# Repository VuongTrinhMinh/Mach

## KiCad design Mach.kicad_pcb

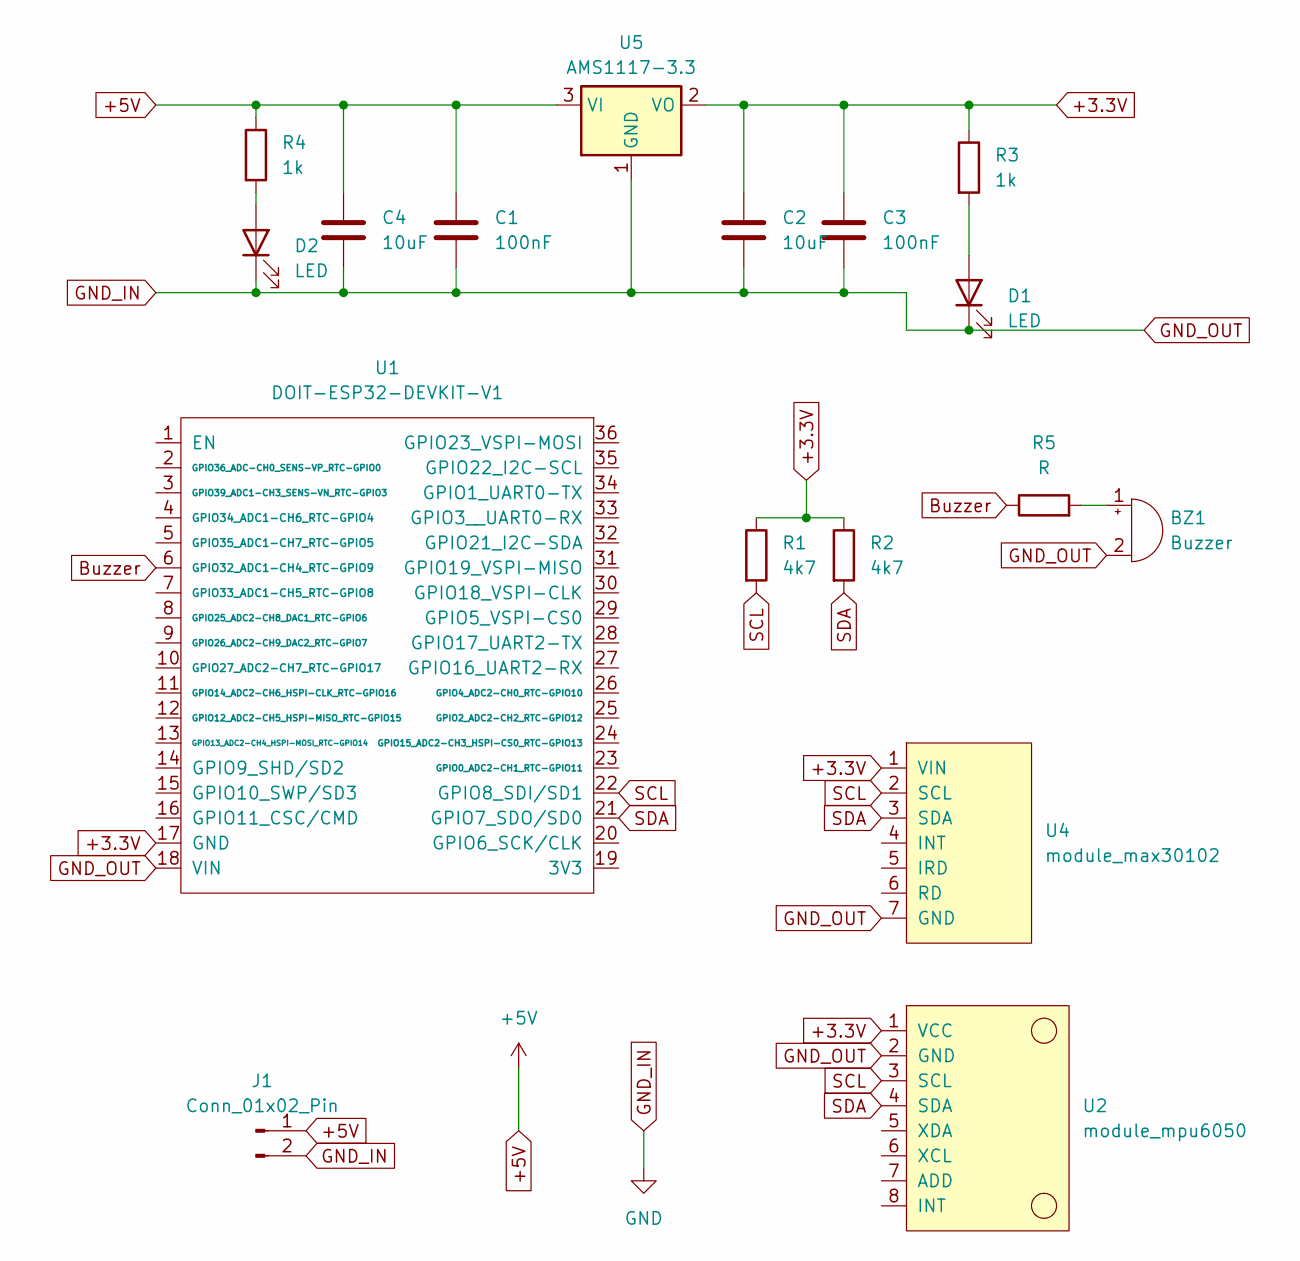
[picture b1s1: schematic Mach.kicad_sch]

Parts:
BZ1: Buzzer; Buzzer_12x9.5RM7.6
C1, C3: 100nF; C_0805_2012Metric
C2, C4: 10uF; C_0805_2012Metric
D1, D2: LED; LED_0805_2012Metric
J1: Conn_01x02_Pin; JST_SH_SM02B-SRSS-TB_1x02-1MP_P1.00mm_Horizontal
R1, R2: 4k7; R_0805_2012Metric
R3, R4: 1k; R_0805_2012Metric
R5: R; R_0805_2012Metric
U1: DOIT-ESP32-DEVKIT-V1; ESP32-DOIT-DEVKIT
U2: module_mpu6050
U4: module_max30102
U5: AMS1117-3.3; SOT-223-3_TabPin2

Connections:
+3.3V: C2.1, C3.1, R1.1, R2.1, R3.1, U1.17 (GND), U2.1 (VCC), U4.1 (VIN), U5.2 (VO)
+5V: C1.1, C4.1, J1.1, R4.1, U5.3 (VI)
Buzzer: R5.1, U1.6 (GPIO32_ADC1-CH4_RTC-GPIO9)
GND_IN: BZ1.2 (-), C1.2, C2.2, C3.2, C4.2, D1.1 (K), D2.1 (K), J1.2, U1.18 (VIN), U2.2 (GND), U4.7 (GND), U5.1 (GND)
unnamed: BZ1.1 (+), R5.2
unnamed: D1.2 (A), R3.2
unnamed: D2.2 (A), R4.2
SCL: R1.2, U1.22 (GPIO8_SDI/SD1), U2.3 (SCL), U4.2 (SCL)
SDA: R2.2, U1.21 (GPIO7_SDO/SD0), U2.4 (SDA), U4.3 (SDA)

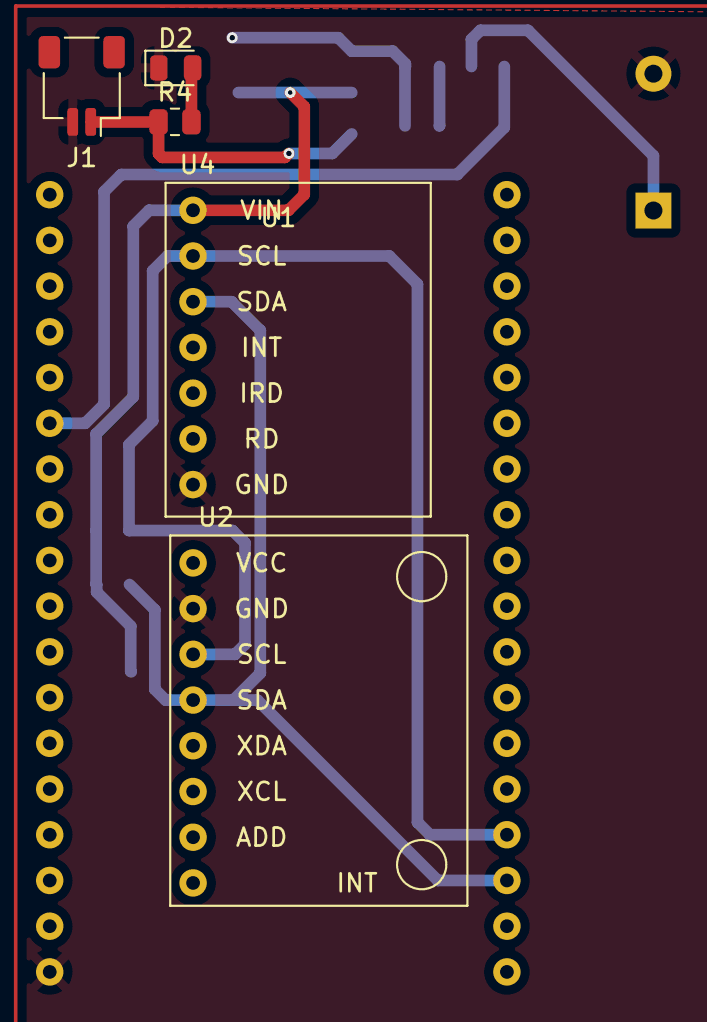
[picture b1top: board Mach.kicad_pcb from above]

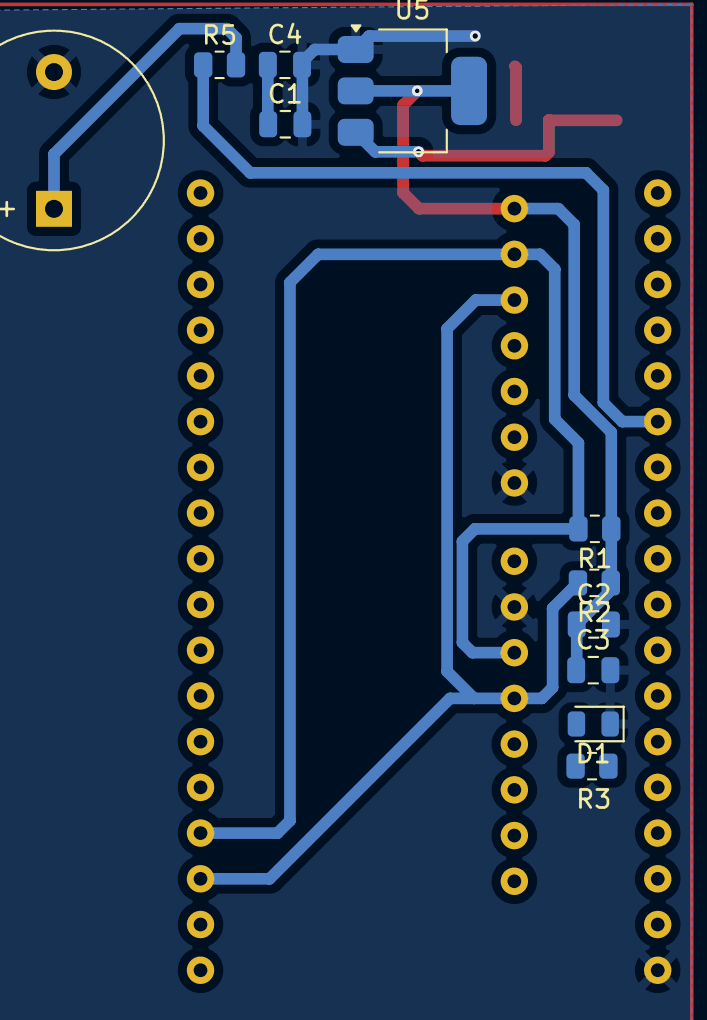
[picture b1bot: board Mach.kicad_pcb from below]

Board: 2 copper layers, 17 parts (11 on the bottom side), 9 nets.
